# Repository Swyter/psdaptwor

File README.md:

# What is `psdaptwor`?
An experimental PC adapter for EPCOT —the PlayStation®VR2 headset— that splits USB Type-C® into DisplayPort video, USB 3 data and power. Intercepting its DP-AUX/SBU and CC side channels.

> **Important**: *This is my first electronics project and I am still ironing the whole thing out, I have gotten here with a lot of hints and reviews from people who actually know what they are doing, but it should be considered non-functional, for now.*

# How do I get one?
Once the project is properly tested and the design is finalized we will provide the manufacturing files to order assembled boards from any affordable printed circuit board (PCB) fabrication house.
The final aim of the project is that one assembled adapter should cost less than 50€; the design and components are being aggresively optimized as much as possible. Getting one or two should be feasible for almost anyone.

# What does it look like?
More or less like this, the dimensions are around *6.3 x 10.2 centimeters*; much tinier than it looks like here:

# What is that name? Do you know how to spell?

No, it is not a typo. I needed something that could be unique and searchable, and contained `PS`, `VR` and `two` somewhere.
Sony products (like the memory card USB one) seem to call their adapters adaptors, so I follow their naming scheme.  

You can call it the *pee ess virtual adaptor*. :)

# Credits and acknowledgements
* *`@JX35`*: For the *DisplayPort AUX emulator* board this is heavily based on, and uncountable references, ideas and suggestions.
* *`@mrandTX`*: Hardware reviews, many suggestions, things I wouldn't have even thought about and encouragement.
* *`@thaytan`, `@ivry.vr` and many others around the Monado project*: Crucial research and development about how the PS®VR2 hardware and software actually functions. Standing on the shoulders of giants, this just cobbles stuff together. Many thanks.
* *[`jorticus/DPSwitch`](https://github.com/jorticus/DPSwitch)*, for the initial DisplayPort symbols and schematic that I used as a start point to learn the program and a good reference of how to use KiCad buses to group signals.
* *[`diva-eng/diva-card`](https://github.com/diva-eng/diva-card)*, for the known-good 12 MHz 20pF crystal oscillator circuit using cheap JLCPCB basic parts, and the capacitor/resistor values.

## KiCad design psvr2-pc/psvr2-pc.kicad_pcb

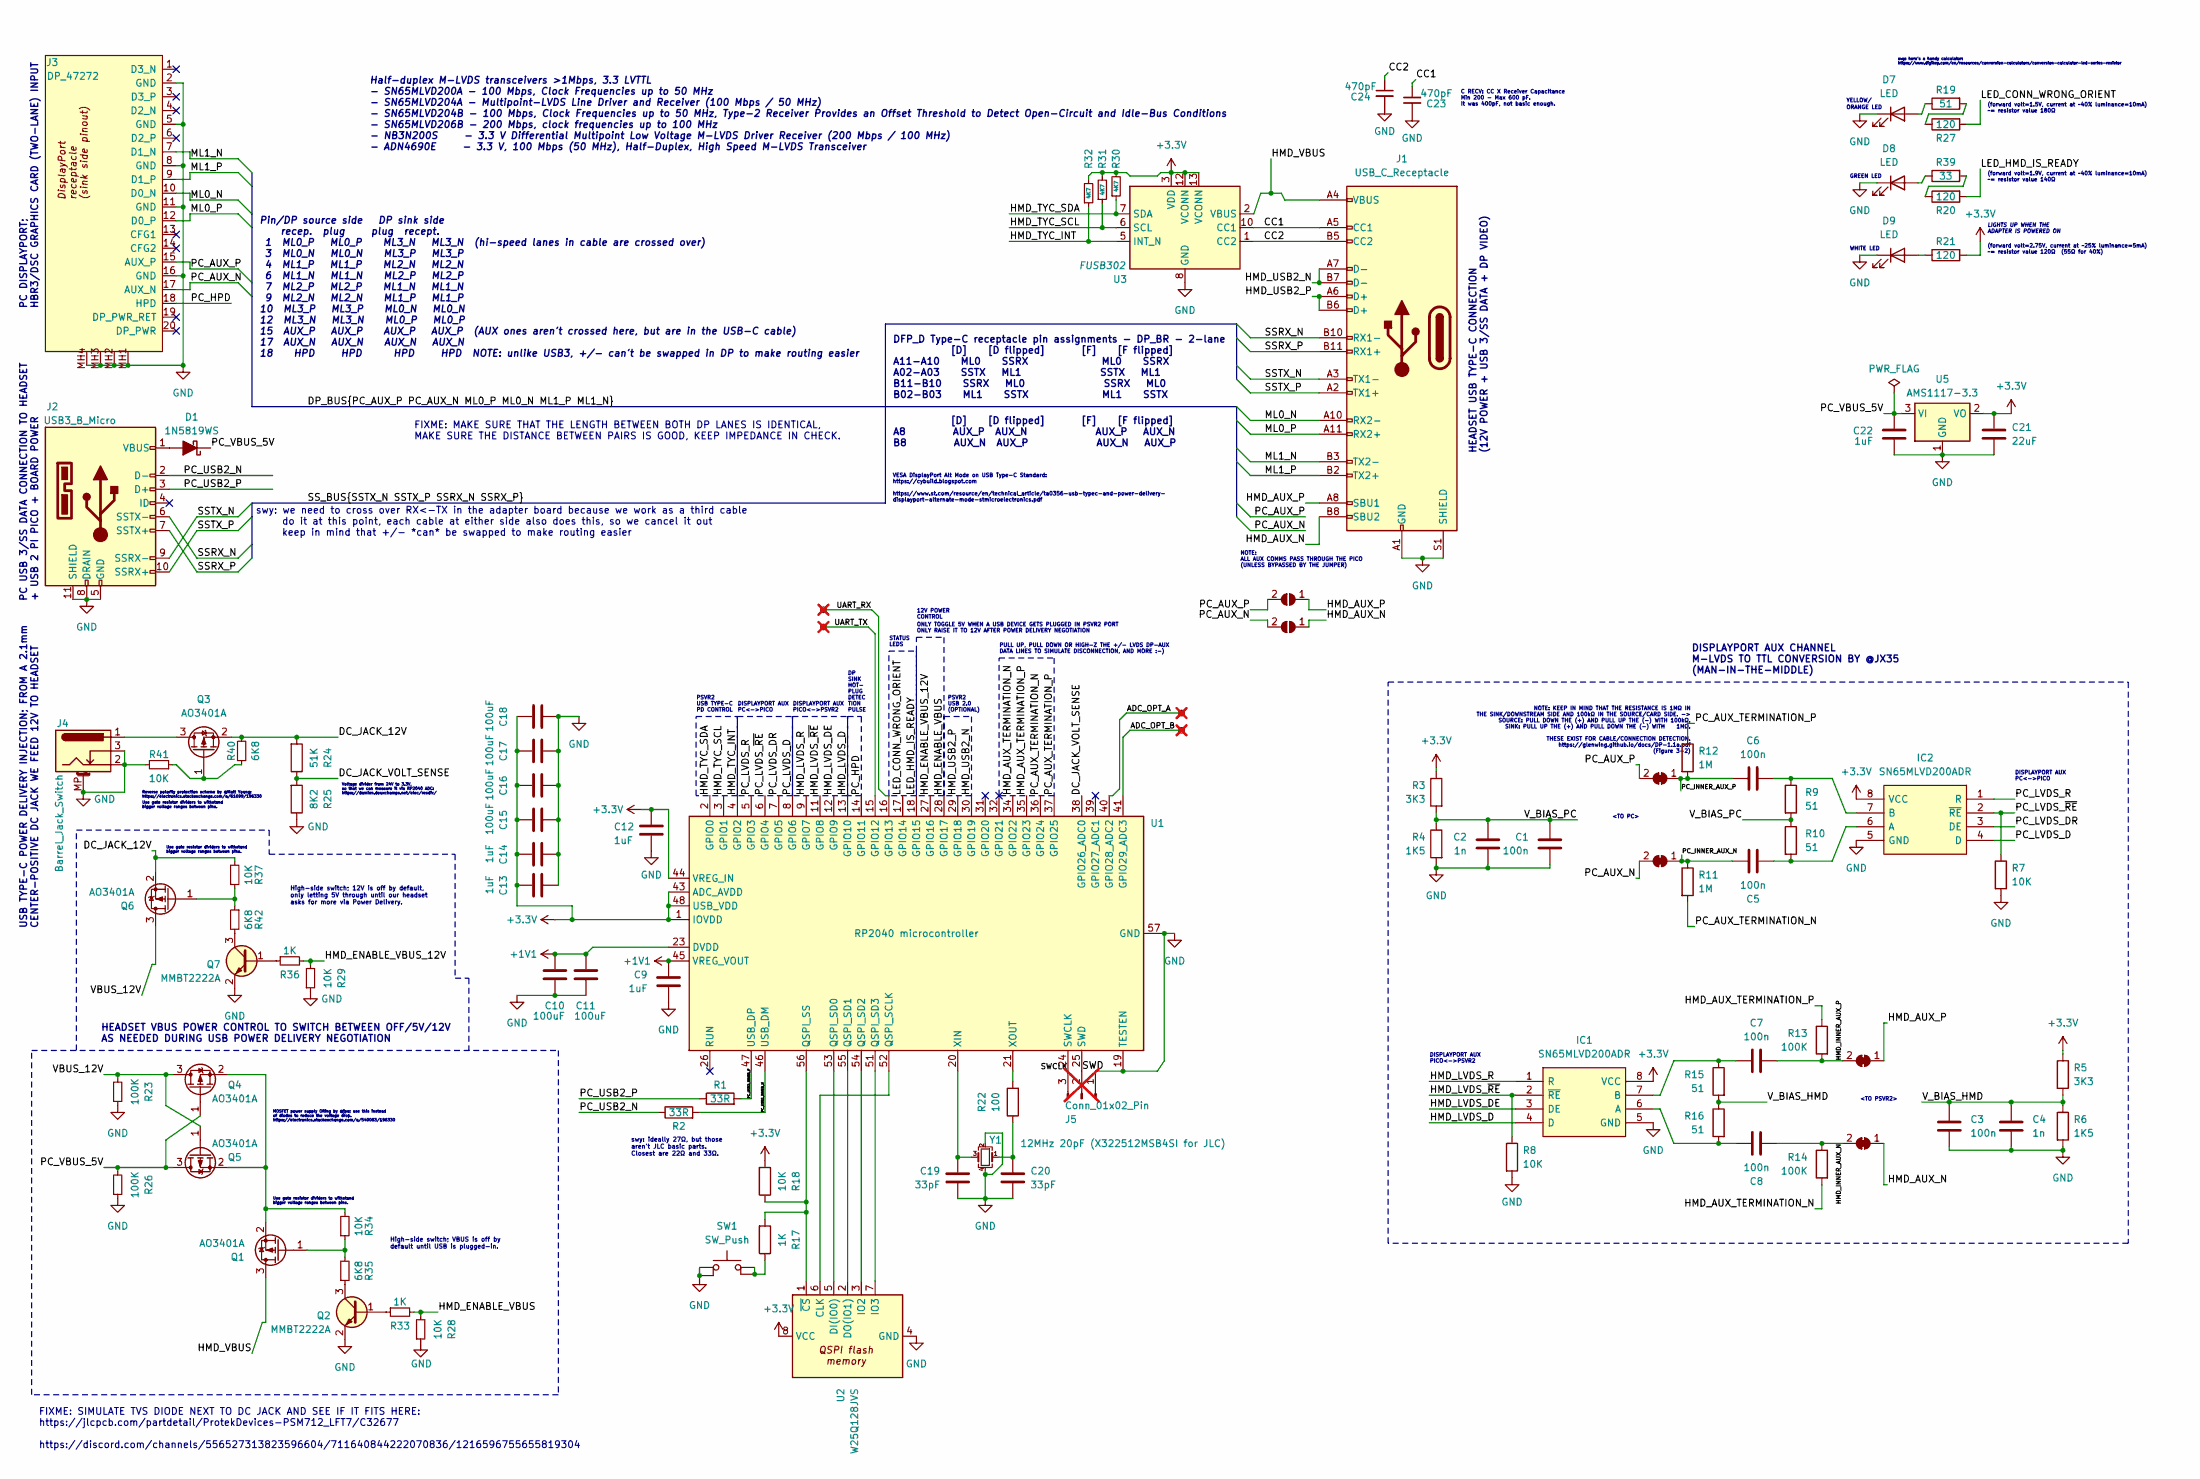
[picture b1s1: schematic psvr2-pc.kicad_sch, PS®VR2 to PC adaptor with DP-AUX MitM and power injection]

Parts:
C1, C3, C5, C6, C7, C8: 100n; C_0805_2012Metric
C2, C4: 1n; C_0805_2012Metric
C9, C12, C13, C14, C22: 1uF; C_0805_2012Metric
C10, C11, C15, C16, C17, C18: 100uF; C_1206_3216Metric
C19: 33pF; C_0603_1608Metric_Pad1.08x0.95mm_HandSolder; Mfr. Part # CL10C330JB8NNNC; LCSC Part # C1663
C20: 33pF; C_0603_1608Metric_Pad1.08x0.95mm_HandSolder; Mfr. Part # CL10C330JB8NNNC; JLCPCB Part # C1663
C21: 22uF; C_0805_2012Metric
C23, C24: 470pF; C_0805_2012Metric; LCSC Part # C1743
D1: 1N5819WS; D_SOD-323; Mfr. Part # 1N5819WS; LCSC Part # C191023
D7: LED; LED_0805_2012Metric; Mfr. Part # KT-0805Y; LCSC Part # C2296
D8: LED; LED_0805_2012Metric; Mfr. Part # KT-0805G; LCSC Part # C2297
D9: LED; LED_0805_2012Metric; Mfr. Part # KT-0805W; LCSC Part # C34499
IC1, IC2: SN65MLVD200ADR; SOIC-8_3.9x4.9mm_P1.27mm; Manufacturer_Part_Number SN65MLVD200ADR; Mouser Part Number 595-SN65MLVD200A
J1: USB_C_Receptacle; USB-C-SMD_TYPE-C-USB-18; Mfr. Part # MOLEX-1054500101; LCSC Part # C134092
J2: USB3_B_Micro; USB-SMD_692622030100
J3: DP_47272; CONN-SMD_472720001; LCSC Part # C587824
J4: Barrel_Jack_Switch; BarrelJack_Horizontal; Mfr. Part # DC-470-2.1GP; LCSC Part # C194407
J5: Conn_01x02_Pin; PinHeader_1x03_P2.54mm_Vertical; not fitted
JP1, JP2: SolderJumper_2_Open; SolderJumper-2_P1.3mm_Open_Pad1.0x1.5mm
JP3, JP5, JP6: SolderJumper_2_CLOSED; SolderJumper-2_P1.3mm_Bridged_RoundedPad1.0x1.5mm
JP4: SolderJumper_2_Open; SolderJumper-2_P1.3mm_Bridged_RoundedPad1.0x1.5mm
Q1, Q3, Q4, Q5, Q6: AO3401A; SOT-23; Mfr. Part # SI2301CDS-T1-GE3; JLCPCB Rotation Offset 180
Q2, Q7: MMBT2222A; SOT-23; Mfr. Part # MMBT2222A 1P; JLCPCB Rotation Offset 180
R1, R2: 33R; R_0805_2012Metric
R3, R5: 3K3; R_0805_2012Metric
R4, R6: 1K5; R_0805_2012Metric
R7, R8, R18, R28, R29, R34, R37, R41: 10K; R_0805_2012Metric
R9, R10, R15, R16, R19: 51; R_0805_2012Metric
R11, R12: 1M; R_0805_2012Metric
R13, R14: 100K; R_1206_3216Metric
R17, R33, R36: 1K; R_0805_2012Metric
R20, R21, R27: 120; R_0805_2012Metric
R22: 100; R_0805_2012Metric
R23, R26: 100K; R_0805_2012Metric
R24: 51K; R_0805_2012Metric
R25: 8K2; R_0805_2012Metric
R30, R31, R32: 4K7; R_0805_2012Metric
R35, R40, R42: 6K8; R_0805_2012Metric
R39: 33; R_0805_2012Metric
SW1: SW_Push; SW-SMD_4P-L5.1-W5.1-P3.70-LS6.5-TL-2; Mfr. Part # TS-1187A-B-A-B; LCSC Part # C318884
TP1, TP2, TP3, TP4: TestPoint_Small; TestPoint_Pad_D2.5mm; not fitted
U1: RP2040 microcontroller; QFN-56-1EP_7x7mm_P0.4mm_EP3.2x3.2mm; Mfr. Part # RP2040; LCSC Part # C2040
U2: W25Q128JVS; SOIC-8_5.23x5.23mm_P1.27mm; Mfr. Part # W25Q128JVSIQ; LCSC Part # C97521
U3: FUSB302B01MPX; WQFN-14-1EP_2.5x2.5mm_P0.5mm_EP1.45x1.45mm; Mfr. Part # Fusb302mpx; LCSC Part # C442699
U5: AMS1117-3.3; SOT-223-3_TabPin2; Mfr. Part # AMS1117-3.3; LCSC Part # C6186
Y1: 12MHz 20pF (X322512MSB4SI for JLC); Crystal_SMD_3225-4Pin_3.2x2.5mm; Mfr. Part # X322512MSB4SI; LCSC Part # C9002

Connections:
+1V1: C9.1, C10.1, C11.1, U1.23 (DVDD), U1.45 (VREG_VOUT), U1.50 (DVDD)
+3.3V: C12.1, C13.2, C14.2, C15.2, C16.2, C17.2, C18.2, C21.1, IC1.8 (VCC), IC2.8 (VCC), R3.1, R5.1, R18.2, R21.2, R30.2, R31.2, R32.2, U1.1 (IOVDD), U1.10 (IOVDD), U1.22 (IOVDD), U1.33 (IOVDD), U1.42 (IOVDD), U1.43 (ADC_AVDD), U1.44 (VREG_IN), U1.48 (USB_VDD), U1.49 (IOVDD), U2.8 (VCC), U3.3 (VDD), U3.4 (VDD), U3.12 (VCONN), U3.13 (VCONN), U5.2 (VO)
/ADC_OPT_A: TP3.1, U1.40 (GPIO28_ADC2)
/ADC_OPT_B: TP4.1, U1.41 (GPIO29_ADC3)
/CC1: C23.1, J1.A5 (CC1), U3.10 (CC1), U3.11 (CC1)
/CC2: C24.1, J1.B5 (CC2), U3.1 (CC2), U3.14 (CC2)
/DC_JACK_12V: Q3.2 (S), Q6.2 (S), R24.2, R37.2, R40.2
/DC_JACK_VOLT_SENSE: R24.1, R25.2, U1.38 (GPIO26_ADC0)
/HMD_AUX_N: J1.B8 (SBU2), JP2.1 (A), JP4.1 (A)
/HMD_AUX_P: J1.A8 (SBU1), JP1.1 (A), JP3.1 (A)
/HMD_AUX_TERMINATION_N: R14.2, U1.34 (GPIO22)
/HMD_AUX_TERMINATION_P: R13.1, U1.35 (GPIO23)
/HMD_ENABLE_VBUS: R28.2, R33.2, U1.28 (GPIO17)
/HMD_ENABLE_VBUS_12V: R29.2, R36.2, U1.27 (GPIO16)
/HMD_INNER_AUX_N: C8.2, JP4.2 (B), R14.1
/HMD_INNER_AUX_P: C7.2, JP3.2 (B), R13.2
/HMD_LVDS_D: IC1.4 (D), U1.13 (GPIO10)
/HMD_LVDS_DE: IC1.3 (DE), U1.12 (GPIO9)
/HMD_LVDS_R: IC1.1 (R), U1.9 (GPIO7)
/HMD_LVDS_~RE: IC1.2 (~RE), R8.1, U1.11 (GPIO8)
/HMD_TYC_INT: R32.1, U1.4 (GPIO2), U3.5 (INT_N)
/HMD_TYC_SCL: R31.1, U1.3 (GPIO1), U3.6 (SCL)
/HMD_TYC_SDA: R30.1, U1.2 (GPIO0), U3.7 (SDA)
/HMD_USB2_N: J1.A7 (D-), J1.B7 (D-), U1.30 (GPIO19)
/HMD_USB2_P: J1.A6 (D+), J1.B6 (D+), U1.29 (GPIO18)
/HMD_VBUS: J1.A4 (VBUS), J1.A9 (VBUS), J1.B4 (VBUS), J1.B9 (VBUS), Q1.3 (D), U3.2 (VBUS)
/LED_CONN_WRONG_ORIENT: R27.2, U1.17 (GPIO14)
/LED_HMD_IS_READY: R20.2, U1.18 (GPIO15)
/ML0_N: J1.A10 (RX2-), J3.10 (D0_N)
/ML0_P: J1.A11 (RX2+), J3.12 (D0_P)
/ML1_N: J1.B3 (TX2-), J3.7 (D1_N)
/ML1_P: J1.B2 (TX2+), J3.9 (D1_P)
/PC_AUX_N: J3.17 (AUX_N), JP2.2 (B), JP6.2 (B)
/PC_AUX_P: J3.15 (AUX_P), JP1.2 (B), JP5.2 (B)
/PC_AUX_TERMINATION_N: R11.2, U1.36 (GPIO24)
/PC_AUX_TERMINATION_P: R12.1, U1.37 (GPIO25)
/PC_HPD: J3.18 (HPD), U1.14 (GPIO11)
/PC_INNER_AUX_N: C5.2, JP6.1 (A), R11.1
/PC_INNER_AUX_P: C6.2, JP5.1 (A), R12.2
/PC_LVDS_D: IC2.4 (D), U1.8 (GPIO6)
/PC_LVDS_DR: IC2.3 (DE), U1.7 (GPIO5)
/PC_LVDS_R: IC2.1 (R), U1.5 (GPIO3)
/PC_LVDS_~RE: IC2.2 (~RE), R7.1, U1.6 (GPIO4)
/PC_USB2_INNER_N: R2.2, U1.46 (USB_DM)
/PC_USB2_INNER_P: R1.2, U1.47 (USB_DP)
/PC_USB2_N: J2.2 (D-), R2.1
/PC_USB2_P: J2.3 (D+), R1.1
/PC_VBUS_5V: C22.1, D1.1 (K), Q4.1 (G), Q5.3 (D), R26.2, U5.3 (VI)
/SSRX_N: J1.B10 (RX1-), J2.6 (SSTX-)
/SSRX_P: J1.B11 (RX1+), J2.7 (SSTX+)
/SSTX_N: J1.A3 (TX1-), J2.9 (SSRX-)
/SSTX_P: J1.A2 (TX1+), J2.10 (SSRX+)
/SWCLK: J5.3, U1.24 (SWCLK)
/SWD: J5.2, U1.25 (SWD)
/UART_RX: TP2.1, U1.16 (GPIO13)
/UART_TX: TP1.1, U1.15 (GPIO12)
/VBUS_12V: Q4.3 (D), Q5.1 (G), Q6.3 (D), R23.2
/V_BIAS_HMD: C3.1, C4.1, R5.2, R6.1, R15.2, R16.1
/V_BIAS_PC: C1.1, C2.1, R3.2, R4.1, R9.2, R10.1
GND: C1.2, C2.2, C3.2, C4.2, C9.2, C10.2, C11.2, C12.2, C13.1, C14.1, C15.1, C16.1, C17.1, C18.1, C19.2, C20.2, C21.2, C22.2, C23.2, C24.2, D7.1 (K), D8.1 (K), D9.1 (K), IC1.5 (GND), IC2.5 (GND), J1.0, J1.A1 (GND), J1.A12 (GND), J1.B1 (GND), J1.B12 (GND), J1.S1 (SHIELD), J2.5 (GND), J2.8 (DRAIN), J2.11 (SHIELD), J3.2 (GND), J3.5 (GND), J3.8 (GND), J3.11 (GND), J3.16 (GND), J3.21, J3.22, J3.23, J3.24, J3.MH1, J3.MH2, J3.MH3, J3.MH4, J4.2, J4.3, J4.MP (MountPin), J5.1, Q2.2 (E), Q7.2 (E), R4.2, R6.2, R7.2, R8.2, R23.1, R25.1, R26.1, R28.1, R29.1, R41.2, SW1.1, SW1.2, U1.19 (TESTEN), U1.57 (GND), U2.4 (GND), U3.8 (GND), U3.9 (GND), U3.15 (GND), U5.1 (GND), Y1.2, Y1.4
unnamed: C20.1, R22.1, Y1.1
unnamed: D1.2 (A), J2.1 (VBUS)
unnamed: D7.2 (A), R19.1
unnamed: D8.2 (A), R39.1
unnamed: D9.2 (A), R21.1
unnamed: C8.1, IC1.6 (A), R16.2
unnamed: C7.1, IC1.7 (B), R15.1
unnamed: C5.1, IC2.6 (A), R10.2
unnamed: C6.1, IC2.7 (B), R9.1
unnamed: Q1.1 (G), R34.1, R35.2
unnamed: Q1.2 (S), Q4.2 (S), Q5.2 (S), R34.2
unnamed: Q2.1 (B), R33.1
unnamed: Q2.3 (C), R35.1
unnamed: J4.1, Q3.3 (D)
unnamed: Q3.1 (G), R40.1, R41.1
unnamed: Q6.1 (G), R37.1, R42.1
unnamed: Q7.1 (B), R36.1
unnamed: Q7.3 (C), R42.2
unnamed: R17.1, SW1.3, SW1.4
unnamed: R19.2, R27.1
unnamed: R20.1, R39.2
unnamed: U1.52 (QSPI_SCLK), U2.6 (CLK)
unnamed: U1.53 (QSPI_SD0), U2.5 (DI(IO0))
unnamed: U1.55 (QSPI_SD1), U2.2 (DO(IO1))
unnamed: U1.54 (QSPI_SD2), U2.3 (IO2)
unnamed: U1.51 (QSPI_SD3), U2.7 (IO3)
unnamed: R17.2, R18.1, U1.56 (QSPI_SS), U2.1 (~CS)
unnamed: C19.1, U1.20 (XIN), Y1.3
unnamed: R22.2, U1.21 (XOUT)

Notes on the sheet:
Reverse polarity protection scheme by @Matt Young: https://electronics.stackexchange.com/a/61699/196330
NOTE: ALL AUX COMMS PASS THROUGH THE PICO (UNLESS BYPASSED BY THE JUMPER)
MOSFET power supply ORing by @jpa; use this instead of diodes to reduce the voltage drop. https://electronics.stackexchange.com/a/549083/196330
VESA DisplayPort Alt Mode on USB Type-C Standard: https://cybuild.blogspot.com https://www.st.com/resource/en/technical_article/ta0356-usb-typec-and-power-delivery- displayport-alternate-mode-stmicroelectronics.pdf
(forward volt=1.5V, current at ~40% luminance=10mA) ~= resistor value 180Ω
C RECV: CC X Receiver Capacitance Min 200 − Max 600 pF. It was 400pF, not basic enough.
DP SINK HOT- PLUG DETEC TION PULSE
HEADSET USB TYPE-C CONNECTION (12V POWER + USB 3/SS DATA + DP VIDEO)
DISPLAYPORT AUX CHANNEL M-LVDS TO TTL CONVERSION BY @JX35 (MAN-IN-THE-MIDDLE)
swy: we need to cross over RX<-TX in the adapter board because we work as a third cable do it at this point, each cable at either side also does this, so we cancel it out keep in mind that +/- *can* be swapped to make routing easier
DISPLAYPORT AUX PICO<->PSVR2
HEADSET VBUS POWER CONTROL TO SWITCH BETWEEN OFF/5V/12V AS NEEDED DURING USB POWER DELIVERY NEGOTIATION
WHITE LED
DISPLAYPORT AUX PC<->PICO
Voltage divider from 24V to 3.3V, so that we can measure it via RP2040 ADC: https://damien.douxchamps.net/elec/resdiv/
<TO PC>
12V POWER CONTROL
FIXME: MAKE SURE THAT THE LENGTH BETWEEN BOTH DP LANES IS IDENTICAL, MAKE SURE THE DISTANCE BETWEEN PAIRS IS GOOD, KEEP IMPEDANCE IN CHECK.
<TO PSVR2>
[D] [D flipped] [F] [F flipped] A8 AUX_P AUX_N AUX_P AUX_N B8 AUX_N AUX_P AUX_N AUX_P
Use gate resistor dividers to withstand bigger voltage ranges between pins.
High-side switch; 12V is off by default, only letting 5V through until our headset asks for more via Power Delivery.
YELLOW/
PULL UP, PULL DOWN OR HIGH-Z THE +/- LVDS DP-AUX DATA LINES TO SIMULATE DISCONNECTION, AND MORE :-)
(forward volt=2.75V, current at ~25% luminance=5mA) ~= resistor value 120Ω (55Ω for 40%)
(forward volt=1.9V, current at ~40% luminance=10mA) ~= resistor value 140Ω
ONLY TOGGLE 5V WHEN A USB DEVICE GETS PLUGGED IN PSVR2 PORT ONLY RAISE IT TO 12V AFTER POWER DELIVERY NEGOTIATION
ORANGE LED
swy: here's a handy calculator: https://www.digikey.com/en/resources/conversion-calculators/conversion-calculator-led-series-resistor
swy: ideally 27Ω, but those aren't JLC basic parts. Closest are 22Ω and 33Ω.
FIXME: SIMULATE TVS DIODE NEXT TO DC JACK AND SEE IF IT FITS HERE: https://jlcpcb.com/partdetail/ProtekDevices-PSM712_LFT7/C32677 https://discord.com/channels/556527313823596604/711640844222070836/1216596755655819304
PSVR2 USB 2.0 (OPTIONAL)
USB TYPE-C POWER DELIVERY INJECTION; FROM A 2.1mm CENTER-POSITIVE DC JACK WE FEED 12V TO HEADSET
Pin/DP source side DP sink side recep. plug plug recept. 1 ML0_P ML0_P ML3_N ML3_N (hi-speed lanes in cable are crossed over) 3 ML0_N ML0_N ML3_P ML3_P 4 ML1_P ML1_P ML2_N ML2_N 6 ML1_N ML1_N ML2_P ML2_P 7 ML2_P ML2_P ML1_N ML1_N 9 ML2_N ML2_N ML1_P ML1_P 10 ML3_P ML3_P ML0_N ML0_N 12 ML3_N ML3_N M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
Half-duplex M-LVDS transceivers >1Mbps, 3.3 LVTTL - SN65MLVD200A - 100 Mbps, Clock Frequencies up to 50 MHz - SN65MLVD204A - Multipoint-LVDS Line Driver and Receiver (100 Mbps / 50 MHz) - SN65MLVD204B - 100 Mbps, Clock Frequencies up to 50 MHz, Type-2 Receiver Provides an Offset Threshold to Detect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
STATUS LEDS
PC USB 3/SS DATA CONNECTION TO HEADSET + USB 2 PI PICO + BOARD POWER
NOTE: KEEP IN MIND THAT THE RESISTANCE IS 1MΩ IN THE SINK/DOWNSTREAM SIDE AND 100kΩ IN THE SOURCE/CARD SIDE. -> SOURCE: PULL DOWN THE (+) AND PULL UP THE (-) WITH 100kΩ. SINK: PULL UP THE (+) AND PULL DOWN THE (-) WITH 1MΩ. THESE EXIST FOR CABLE/CONNECTION DETECTION. https://glenwing.github.io/docs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
High-side switch; VBUS is off by default until USB is plugged-in.
DFP_D Type-C receptacle pin assignments - DP_BR - 2-lane [D] [D flipped] [F] [F flipped] A11-A10 ML0 SSRX ML0 SSRX A02-A03 SSTX ML1 SSTX ML1 B11-B10 SSRX ML0 SSRX ML0 B02-B03 ML1 SSTX ML1 SSTX

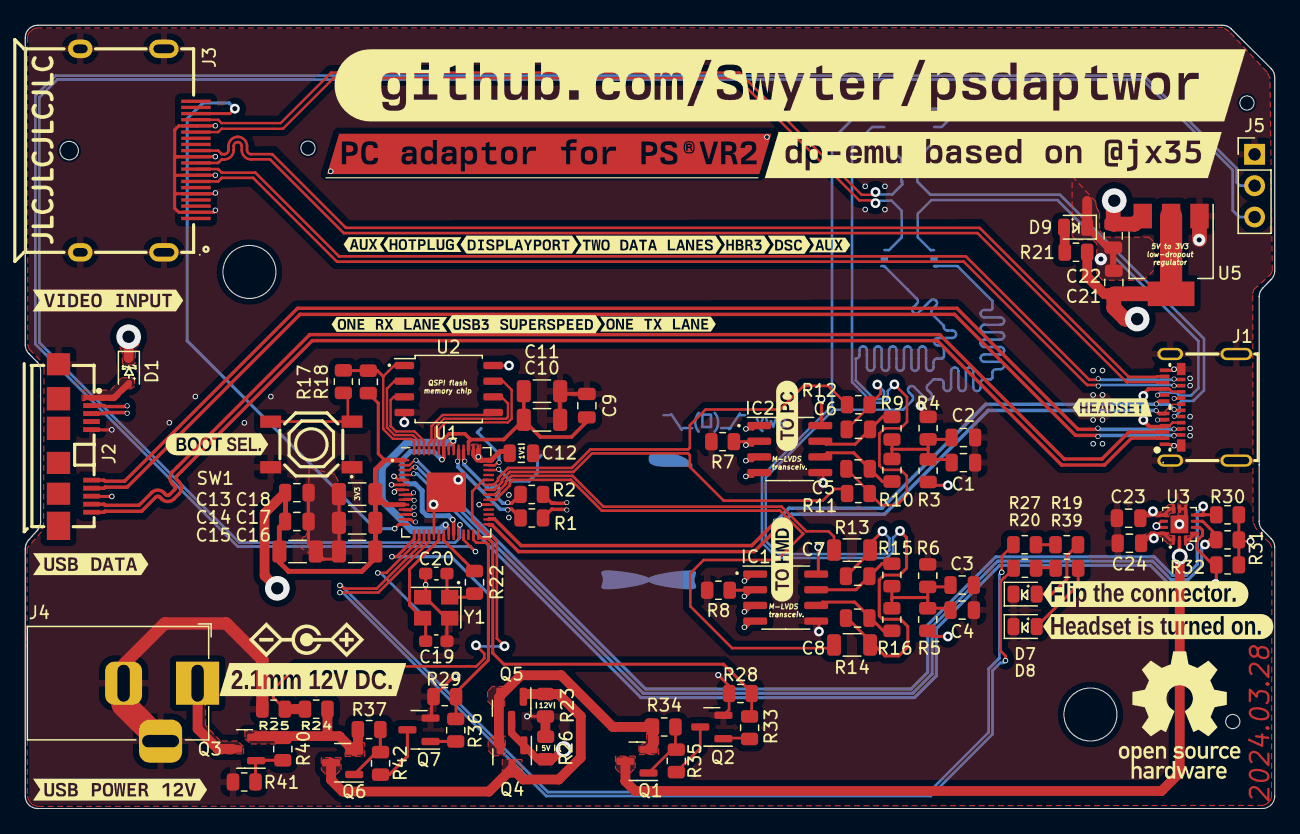
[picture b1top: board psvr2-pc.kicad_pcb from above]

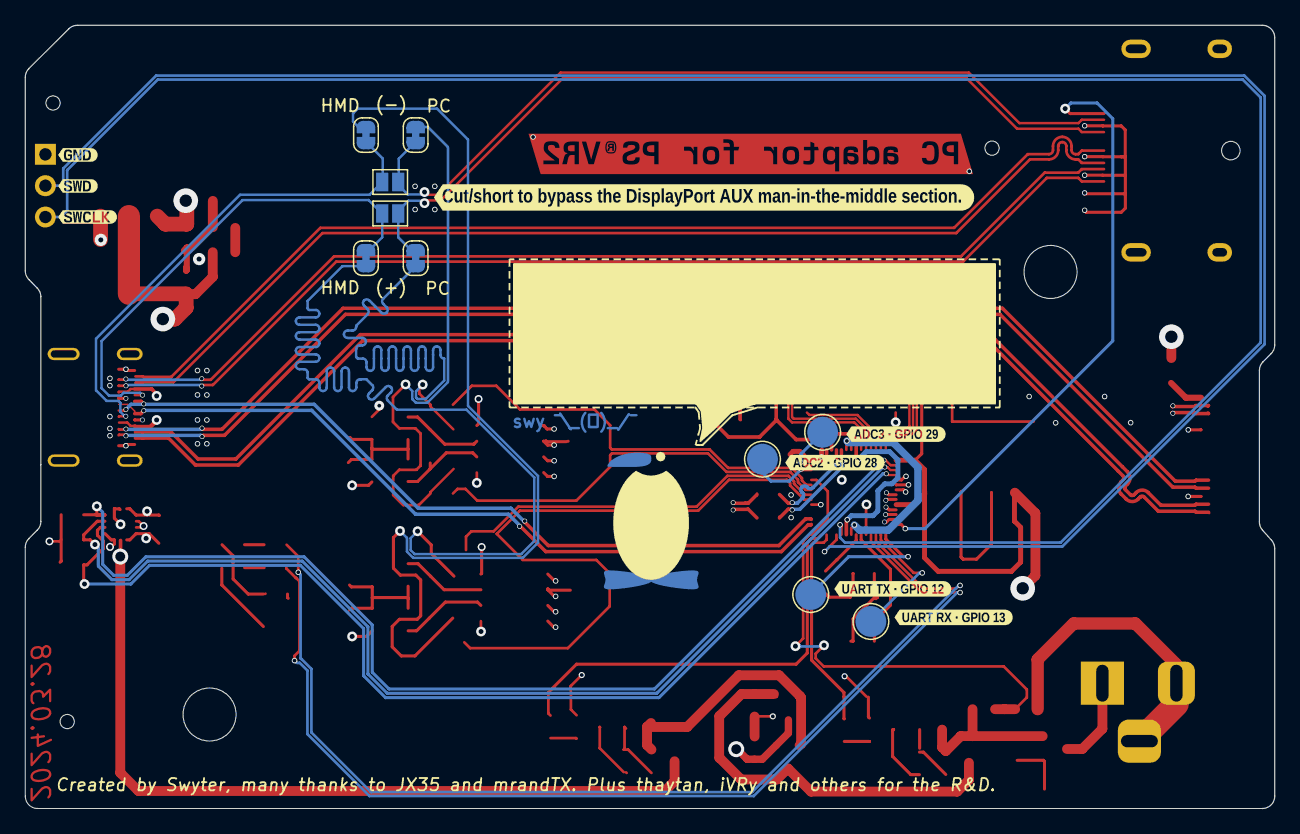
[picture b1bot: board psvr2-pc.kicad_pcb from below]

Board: 4 copper layers, 101.3 x 63.5 mm, 135 parts (18 on the bottom side), 89 nets.

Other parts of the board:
M4_MOUNT_HOLE_DOWN, M4_MOUNT_HOLE_UP: MountingHole_4.3mm_M4
SMT_BOTTOM_RIGHT: MountingHole_2.1mm
SMT_TOP_LEFT: MountingHole_2.1mm
SMT_TOP_RIGHT: MountingHole_2.1mm
kibuzzard-65C6E5E2: G***; kibuzzard-65C6E5E2
kibuzzard-65C6E540: G***; kibuzzard-65C6E540
kibuzzard-65C0700D: G***; kibuzzard-65C0700D
kibuzzard-65C07004: G***; kibuzzard-65C07004
kibuzzard-65C07017: G***; kibuzzard-65C07017
kibuzzard-65E1F822: G***; kibuzzard-65E1F822
kibuzzard-65E1F853: G***; kibuzzard-65E1F853
kibuzzard-65E1FEE7: G***; kibuzzard-65E1FEE7
kibuzzard-65E1FEEE: G***; kibuzzard-65E1FEEE
kibuzzard-65E1FFC8: G***; kibuzzard-65E1FFC8
kibuzzard-65E7A09E: G***; kibuzzard-65E7A09E
kibuzzard-65E7A091: G***; kibuzzard-65E7A091
kibuzzard-65E7B531: G***; kibuzzard-65E7B531
kibuzzard-65E009D7: G***; kibuzzard-65E009D7
kibuzzard-65E024DE: G***; kibuzzard-65E024DE
kibuzzard-65E0054E: G***; kibuzzard-65E0054E
kibuzzard-65E91FE7: G***; kibuzzard-65E91FE7
kibuzzard-65E539B1: G***; kibuzzard-65E539B1
kibuzzard-65E00649: G***; kibuzzard-65E00649
kibuzzard-65E00656: G***; kibuzzard-65E00656
kibuzzard-65E00723: G***; kibuzzard-65E00723
kibuzzard-65E00862: G***; kibuzzard-65E00862
kibuzzard-65E00873: G***; kibuzzard-65E00873
kibuzzard-65E00902: G***; kibuzzard-65E00902
kibuzzard-65E00968: G***; kibuzzard-65E00968
kibuzzard-65E01491: G***; kibuzzard-65E01491
kibuzzard-65E20367: G***; kibuzzard-65E20367
kibuzzard-65EB850B: G***; kibuzzard-65EB850B
kibuzzard-65EB8511: G***; kibuzzard-65EB8511
kibuzzard-65F67D58: G***; kibuzzard-65F67D58
kibuzzard-65F683C1: G***; kibuzzard-65F683C1

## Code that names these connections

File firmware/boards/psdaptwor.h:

/**
 * | psdaptwor - an experimental PSVR2 to PC adaptor | custom RP2040 board pinout and boot-up defines
 * | created by Swyter <swyterzone+psdaptwor@gmail.com>
 *
 * SPDX-License-Identifier: GPL-2.0-or-later
 */

// -----------------------------------------------------
// NOTE: THIS HEADER IS ALSO INCLUDED BY ASSEMBLER SO
//       SHOULD ONLY CONSIST OF PREPROCESSOR DIRECTIVES
// -----------------------------------------------------

#ifndef _BOARDS_SWYTER_PSDAPTWOR_RP2040_H
#define _BOARDS_SWYTER_PSDAPTWOR_RP2040_H

// For board detection
#define SWYTER_PSDAPTWOR_RP2040

// On some samples, the xosc can take longer to stabilize than is usual
#ifndef PICO_XOSC_STARTUP_DELAY_MULTIPLIER
#define PICO_XOSC_STARTUP_DELAY_MULTIPLIER 64
#endif

//------------- UART -------------//
#ifndef PICO_DEFAULT_UART
#define PICO_DEFAULT_UART 0 /* swy: we need to use [UART HW BLOCK 0] for GPIO12 and GPIO13, it's the only function that can be used in those pins; [UART HW BLOCK 1] won't work here */
#endif

#ifndef PICO_DEFAULT_UART_TX_PIN
#define PICO_DEFAULT_UART_TX_PIN 12 /* swy: GPIO12 */
#endif

#ifndef PICO_DEFAULT_UART_RX_PIN
#define PICO_DEFAULT_UART_RX_PIN 13 /* swy: GPIO13 */
#endif

//------------- LED -------------//
#ifndef PICO_DEFAULT_LED_PIN
#define PICO_DEFAULT_LED_PIN 14 /* swy: GPIO14, also known as PSDAPT_PIN_LED_CONN_WRONG_ORIENT */
#endif

//------------- I2C -------------//
#ifndef PICO_DEFAULT_I2C
#define PICO_DEFAULT_I2C 0 /* swy: important: we need to use [I2C HW Block 0], which is the only function that works for GPIO0 and GPIO1. [I2C HW Block 1] won't do anything unless you change pins; see the diagram in gpio.h */
#endif

#ifndef PICO_DEFAULT_I2C_SDA_PIN
#define PICO_DEFAULT_I2C_SDA_PIN 0 /* swy: GPIO0 */
#endif

#ifndef PICO_DEFAULT_I2C_SCL_PIN
#define PICO_DEFAULT_I2C_SCL_PIN 1 /* swy: GPIO1 */
#endif

//------------- FLASH -------------//

// Use slower generic flash access
#define PICO_BOOT_STAGE2_CHOOSE_GENERIC_03H 1

#ifndef PICO_FLASH_SPI_CLKDIV
#define PICO_FLASH_SPI_CLKDIV 4
#endif

#ifndef PICO_FLASH_SIZE_BYTES
#define PICO_FLASH_SIZE_BYTES (16 * 1024 * 1024) /* swy: 16 MiB for the W25Q128JVSIQ flash chip, or 128 Mbits in manufacturer lingo */
#endif

// All boards have B1 RP2040
#ifndef PICO_RP2040_B0_SUPPORTED
#define PICO_RP2040_B0_SUPPORTED 0
#endif

#endif

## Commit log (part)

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2024-02-01 First commit, we'll see how it goes. I don't know what I'm doing.
2024-02-01 Start labeling the buses and actually wiring the nets somewhat.
2024-02-04 Start documenting the valid half-duplex M-LVDS transceivers >1Mbps that work for converting the differential DP-AUX signals into something that the microcontroller GPIO can understand.
2024-02-04 Mess around with the footprint downloader, can't seem to get 3D models out of anything that I can actually pick from the Chinese site. ¯\_(ツ)_/¯
2024-02-05 Improve the schematic and fix some DRC issues.
2024-02-05 Learn to work in multiple copper layers. Swap a differential pair at the beginning. Leave a ground plane sandwiched in the middle and always keep the high speed signals at both extremes.
2024-02-06 Making it all worse due to the SSTX <-> SSRX crossing. The good thing is that the positive and negative wires in each individual lane can be swapped to make routing easier.
2024-02-10 Add a neat line under the "for PS VR2" copper art and highlight it.
2024-02-13 Work a bit more on the 12V-switching MOSFET that powers the headset.
2024-02-14 Finish the LVDS line and pasives, straight-up copying what @jx35 made in his schematic. I think it was based on some Intel motherboard design.
2024-02-14 Make the oscillator thingie better, grabbed the capacitor/resistor values from a known working board for JLC's YSX321SL:
    https://www.reddit.com/r/PrintedCircuitBoard/comments/vtjyqg/thanks_for_all_your_help_my_first_pcb_design_is/
    https://raw.githubusercontent.com/diva-eng/diva-card/main/schematic.pdf
2024-02-24 Connect the USB 2.0 lines to the RP2040 so that it can be potentially be used with PIO as a host/hub, in case it's needed. Make it all programmable and flexible in software, just in case.
2024-02-24 Forgot to mark the solder jumpers in the DP-AUX part as closed/bridged, let me change it. Tidy up some of the wires to make it prettier. ¯\_(ツ)_/¯
2024-02-25 Start fixing some stuff in the schematic after some @JX35 feedback; try to fix the MOSFET power switch section and add some much-needed resistors. still need to properly simulate the whole power circ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
    - The 12V feedback resistors look to small to me, they'd burn 200mW at 12V; small SMD resistors can't handle that and it's a waste
    - The FUSB302 datasheet specifies 4K7 external pullups on the communication lines, I'd add them because internal pullups of MCUs are usually quite weak. It also specifies tiny capacitors on
2024-02-26 Mess around trying to give every component some kind of footprint, even if they are too big and impractical right now, to get a good intuition of what we would need to do, board-size wise.
2024-02-29 Learning how to route components hopefully in a practical and symmetrical way. As a fan of puzzle games, this stuff is pretty relaxing. We'll see how I mess it up.
2024-02-29 PCB. Connecting people. ¯\_(ツ)_/¯
2024-02-29 Start routing things like power. And more tentative GPIO.
2024-02-29 More routing improvements over the third layer for the LVDS.
2024-02-29 More changes, I honestly forgot what.
2024-03-01 Try to fix the third layer (power plane) to actually have a ground fill under/over the high-speed differential lines. route the SWD/SWCLK lines.
2024-03-01 Fix some overlapping component tags and make them readable. No more DRC errors or warnings. Yay! The next step is to look again at the schematic and flesh out the component footprints, double check t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
2024-03-01 Increase the via size to where it makes sense, and space is not too constrained. Mostly to .4mm, make the power vias also thicker. Fix the 90-degree corners in the AUX LVDS terminator traces, like Ma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
    > Nice. Minor comments: It's difficult to tell from the image, but the vias seems surprisingly close to the pads for U1 and U2. Guessing it's probably fine, and it just looks worse than it is. Even f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
2024-03-03 Add the JLC component number for the SPI flash chip, and add 3D models to the LVDS and flash chips in the PCB editor. These Internet footprints seem to be pretty terrible all around.
2024-03-04 Make the filled out areas in all the layers more comprehensive, rounded, and giving enough margin from the cutout area to avoid shorting stuff out, like @mrandTX mentioned. Thanks to him.
2024-03-04 Less is more; reroute the power layer 5V rail over the top-right edge, all around. Between the 3V3 and ground. Don't interrupt the ground fill. I'll use layer two to route the DP-AUX traces, as the h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
2024-03-06 Switch the footprint of the oscillator capacitors from 0805 to the smaller 0603 shape, add part numbers. As those are "basic" parts on JLC. Name the inner AUX traces before the jumpers so that we can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
2024-03-06 I honestly don't remember what changed. :)
2024-03-06 Explain the weird name and add a pronunciation guide.
2024-03-07 Move more or the HMD_LVDS_* lines next to the the microcontroller. Make the vias more far apart.
2024-03-07 Get rid of the pin header 3D model by setting the scale to zero, fix the courtyard a bit, don't include it in the bill of materials: https://forum.kicad.info/t/how-to-remove-3d-model-but-keep-pads/28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
2024-03-08 Make the 1V1 and 3V3 power rails next to the microcontroller thicker. Add little dots to mark pin one of each chip; lines are too subtle for me. Add more silkscreened hidden/easter eggs under a few c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
2024-03-09 Switch the footprint of the 100uF capacitors from 0805 to 1206. As those are listed as "basic", unfortunately making the layout more cluttered and ugly, for now.
2024-03-09 Fix the footprints in the schematic part, I only changed them in the PCB, so when sync'ing the schematic to the PCB it was erroring out and these components were skipped altogether. Add more LCSC par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
2024-03-10 Great, this doesn't work anymore after using the real library model. I'll need to see what's going on.
2024-03-11 I know why the simulation didn't work; I applied the P-MOSFET model to the Q6/HMD_ENABLE_BUS NPN transistor. I'm stupid, as usual. :)
2024-03-17 Mess around a bit more with the simulation. can't say I really know what's wrong or why the simulation isn't clamping anything. Worth studying more in the future.
2024-03-17 Use the MMBT2222A NPN transistor to toggle the P-MOSFET gates low. These use the SOT-3 footprint, but the pins are switched around; base is pin 1, emitter 2 and collector is 3. Had to rewire the PCB 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
2024-03-17 Matched the length between SS RX and TX pairs (probably optional) and more importantly, between the ML0 and ML1 lanes for DisplayPort, as these work in parallel. Find the longer pair, and use it as t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
2024-03-18 Make the 5 volt USB trace straight from the pin ultra thick, if this is going to also feed the headset, let there be current.
2024-03-20 Use relative paths to retrieve the 3D models. Get rid of the ugly EasyEDA watermarks in the models with the help from FreeCAD.
    Download the more fleshed out 3D model for the USB-C receptacle with actually-modeled pins from SnapEDA, the official one from Molex sucks: https://www.snapeda.com/parts/105450-0101/Molex/view-part/?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
2024-03-21 Use a 22uF output capacitor for the 5V to 3V3 LDO voltage regulator. Update the preview image.
2024-03-28 Make the 5V VBUS trace thicker to be able to sink more current.
2024-04-09 Firmware: Edit the custom board pinout to add GPIO12 as UART TX, GPIO13 as UART RX (these are exposed as test pads in the backside), GPIO15 for the default LED. And GPIO0 for I2C SDA and GPIO1 for I2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
2024-04-10 Firmware: Add some VS Code voodoo to be able to do self-debugging, by using the second Arm core, we lose USB serial output, though: https://github.com/majbthrd/pico-debug/
2024-04-10 Firmware: Make everything more readable, license the firmware as GPL-2.0-or-later.
2024-04-11 Firmware: Use the `i2c_read_blocking_until()` function, with a generous timeout. Re-enable the internal pull-up resistors and wait for 3.5 seconds on startup to be able to monitor the USB serial outp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
2024-04-12 Firmware: Add the FUSB302 USB-C controller register file from https://github.com/Ralim/usb-pd/blob/609dda7d16a5d572b87794f4fd3b3c01f1bfd1f8/src/fusb302_defines.h#L3.
2024-04-12 Firmware: Made some progress with detecting the MOSFETS switching on and off (see the gpio_put(PSDAPT_PIN_HMD_ENABLE_VBUS)) with the FUSB controller, while I can't get the measured voltage on that si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
    GPIO 0: 1 1: 1 2: 0 3: 0 4: 0 5: 0
    Raw value: 0x832, measured voltage: 1.690283 V, actual pre-divided voltage: 12.292969 V
    f write ret: 0
    i2c_read FUSB_MEASURE: 0x40
    i2c_read FUSB_STATUS0: 0xa0
    gpio_is_pulled_down: 1
2024-04-15 Firmware: Start working on measuring the CC1 and CC2 (configuration channel) line voltages to see the type-C plug orientation. Do it while still having a working VBUS voltage measurement interleaved.
2024-04-15 Firmware: Factor out the CC1 and CC2 check into fusb_compare_cc1_and_cc2() function. More cleanups. Change how LEDs work.
2024-04-16 Firmware: Try to make the BMC receiver work, as a sink, and get some RX packets from the FIFO register. I got a 0x7 byte one time, that's progress. Start working on using bit tiddling individual regi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
2024-04-17 Firmware: Add support for printing the FUSB_POWER and FUSB_CONTROL* registers. For some reason the stdio output is clipping on interrupts. Fix the 0b binary prefix in headers. I wrote 0xb by mistake 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
    f write ret: 0
    [INTERRUPTB]: 0, [INTERRUPT]: I_VBUSOK,
    [STATUS0]: VBUSOK|BC_LVL1|BC_LVL0,
    [STATUS0A]: POWER3|POWER2,
    [SWITCHES0]: PDWN_2|PDWN_1,
    [SWITCHES1]: SPECREV0,
2024-04-17 Firmware: Port over more CC pin state retrieval logic and resistor state, which is used to get the maximum amperage.
2024-04-17 Firmware: Getting a little bit closer receiving random BMC packets far in between. I believe. Still sweating bullets.
    [adc] Raw value: 0x01e, measured voltage: 0.024170 V, actual pre-divided voltage: 0.175781 V
    i2c_read_blocking; 3; ; get_num_bytes 0; i2c_read_blocking b; 4; get_message: ret=0, buf=0, header=0
    [adc] Raw value: 0x01e, measured voltage: 0.024170 V, actual pre-divided voltage: 0.175781 V
    i2c_read_blocking; 3; ; get_num_bytes 4; i2c_read_blocking b; 8; get_message: ret=0, buf=36019096, header=11a1
    [adc] Raw value: 0x01d, measured voltage: 0.023364 V, actual pre-divided voltage: 0.169922 V
    i2c_read_blocking; 3; ; get_num_bytes 0; i2c_read_blocking b; 4; get_message: ret=0, buf
2024-04-17 Firmware: Move the printf() stuff out of the interrupt handler, just set a boolean and in do it in the main loop, fixes the weirdness and somewhat getting stuck, sometimes. Clean up the serial input 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
2024-04-23 Firmware: Finish parsing the Power Delivery message header fields, separate the hex dump uint32 bytes for readability. Start parsing the SOURCE_CAPABILITIES data objects.
    ---- Opened the serial port COM4 ----
    I2C Bus Scan test
    0 1 2 3 4 5 6 7 8 9 A B C D E F
    00 . . . . . . . . . . . . . . . .
    10 . . . . . . . . . . . . . . . .
    20 . . @ . . . . . . . . . . . . .
2024-04-23 Firmware: Only change polarity when needed. Try to search for Power Delivery messages in the FIFO RX buffer when we get an FUSB_INTERRUPT_I_CRC_CHK interrupt, doesn't seem to work great. Here's a ran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
    ---- Closed the serial port COM4 ----
    ---- Opened the serial port COM4 ----
    I2C Bus Scan test
    0 1 2 3 4 5 6 7 8 9 A B C D E F
    00 . . . . . . . . . . . . . . . .
    10 . . . . . . . . . . . . . . . .
2024-04-23 Firmware: Trying to figure out why transmitting doesn't work, not even a simple GoodCRC message, probably timing. Flush the FIFO on send_message(), log the FIFO fill state in STATUS1. Disable FUSB_SW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
2024-04-24 Firmware: Second try, let's overclock the RP2040 to 160MHz, just to have more leeway. Start rewriting receiving packets.
2024-04-24 Firmware, Binary Template: Show the capabilities power objects in a friendly way.
